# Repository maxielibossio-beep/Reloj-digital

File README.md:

# Reloj-digital
Pcb, esquematico y simulacion del reloj digital

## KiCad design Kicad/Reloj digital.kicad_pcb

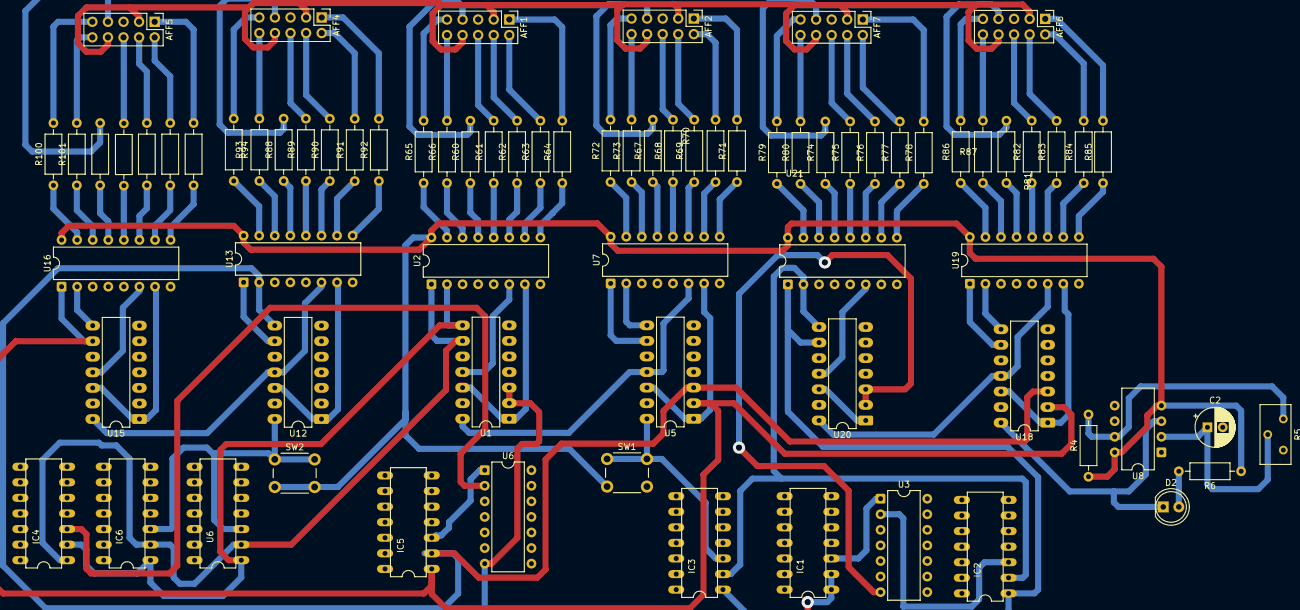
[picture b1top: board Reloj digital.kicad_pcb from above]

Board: 2 copper layers, 77 parts (0 on the bottom side), 125 nets.

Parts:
AFF1, AFF2, AFF4, AFF5, AFF6, AFF7: LTS-6980HR; PinHeader_2x05_P2.54mm_Vertical
C2: 100uF; CP_Radial_D6.3mm_P2.50mm
D2: LED; LED_D5.0mm
IC1, IC2, IC3, IC4, IC5, IC6: 74LS08; DIL14
R4: 4,7KΩ; R_Axial_DIN0207_L6.3mm_D2.5mm_P10.16mm_Horizontal
R5: 10kΩ; Potentiometer_Bourns_3296Y_Vertical
R6: 220Ω; R_Axial_DIN0207_L6.3mm_D2.5mm_P10.16mm_Horizontal
R60, R61, R62, R63, R64, R65, R66, R67, R68, R69, R70, R71, R72, R73, R74, R75, R76, R77, R78, R79, R80, R81, R82, R83, R84, R85, R86, R87, R88, R89, R90, R91, R92, R93, R94, R95, R96, R97, R98, R99, R100, R101: 330R; R_Axial_DIN0207_L6.3mm_D2.5mm_P10.16mm_Horizontal
SW1, SW2: SW_Push; SW_PUSH_6mm
U1, U5, U12, U15, U18, U20: 74LS90; DIP-14_W7.62mm_LongPads
U2, U7, U13, U16, U19, U21: 74LS47; DIP-16_W7.62mm
U3, U6: 74AUC2G32; DIP-14_W7.62mm
U6#2: 74LS08; DIL14
U8: 555; CERDIP-8_W7.62mm_SideBrazed

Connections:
CKA: D2.1 (K), U8.3 (Output), U18.14 (CP0)
GND: C2.2, U1.6 (R9(1)), U1.7 (R9(2)), U2.8 (GND), U5.6 (R9(1)), U5.7 (R9(2)), U7.8 (GND), U8.1 (GND), U12.6 (R9(1)), U12.7 (R9(2)), U13.8 (GND), U15.6 (R9(1)), U15.7 (R9(2)), U16.8 (GND), U18.6 (R9(1)), U18.7 (R9(2)), U19.8 (GND), U20.6 (R9(1)), U20.7 (R9(2)), U21.8 (GND)
unnamed: AFF1.7 (a), R60.2
unnamed: AFF1.6 (b), R61.2
unnamed: AFF1.4 (c), R62.2
unnamed: AFF1.2 (d), R63.2
unnamed: AFF1.1 (e), R64.2
unnamed: AFF1.9 (f), R65.2
unnamed: AFF1.10 (g), R66.2
unnamed: AFF2.7 (a), R67.2
unnamed: AFF2.6 (b), R68.2
unnamed: AFF2.4 (c), R69.2
unnamed: AFF2.2 (d), R70.2
unnamed: AFF2.1 (e), R71.2
unnamed: AFF2.9 (f), R72.2
unnamed: AFF2.10 (g), R73.2
unnamed: AFF4.7 (a), R88.2
unnamed: AFF4.6 (b), R89.2
unnamed: AFF4.4 (c), R90.2
unnamed: AFF4.2 (d), R91.2
unnamed: AFF4.1 (e), R92.2
unnamed: AFF4.9 (f), R93.2
unnamed: AFF4.10 (g), R94.2
unnamed: AFF5.7 (a), R95.2
unnamed: AFF5.6 (b), R96.2
unnamed: AFF5.4 (c), R97.2
unnamed: AFF5.2 (d), R98.2
unnamed: AFF5.1 (e), R99.2
unnamed: AFF5.9 (f), R100.2
unnamed: AFF5.10 (g), R101.2
unnamed: AFF6.7 (a), R81.2
unnamed: AFF6.6 (b), R82.2
unnamed: AFF6.4 (c), R83.2
unnamed: AFF6.2 (d), R84.2
unnamed: AFF6.1 (e), R85.2
unnamed: AFF6.9 (f), R86.2
unnamed: AFF6.10 (g), R87.2
unnamed: AFF7.7 (a), R74.2
unnamed: AFF7.6 (b), R75.2
unnamed: AFF7.4 (c), R76.2
unnamed: AFF7.2 (d), R77.2
unnamed: AFF7.1 (e), R78.2
unnamed: AFF7.9 (f), R79.2
unnamed: AFF7.10 (g), R80.2
unnamed: D2.2 (A), R6.2
unnamed: IC1.3, U3.1
unnamed: IC2.3, U3.2
unnamed: IC4.3, U6.2
unnamed: IC5.3, U6.1
unnamed: AFF1.3 (C.K.), AFF1.8 (C.K.), AFF2.3 (C.K.), AFF2.8 (C.K.), AFF4.3 (C.K.), AFF4.8 (C.K.), AFF5.3 (C.K.), AFF5.8 (C.K.), AFF6.3 (C.K.), AFF6.8 (C.K.), AFF7.3 (C.K.), AFF7.8 (C.K.)
unnamed: U1.14 (CP0), U5.11 (Q3), U7.6 (D)
unnamed: U1.1 (CP1..3), U1.12 (Q0), U2.7 (A)
unnamed: IC4.1, IC6.2, U1.9 (Q1), U2.1 (B), U6#2.2
unnamed: IC4.2, IC6.1, U1.8 (Q2), U2.2 (C), U6#2.1
unnamed: U1.11 (Q3), U2.6 (D)
unnamed: IC1.1, IC1.2, U1.2 (R0(1)), U1.3 (R0(2)), U6.7
unnamed: R60.1, U2.13 (a)
unnamed: R61.1, U2.12 (b)
unnamed: R62.1, U2.11 (c)
unnamed: R63.1, U2.10 (d)
unnamed: R64.1, U2.9 (e)
unnamed: R65.1, U2.15 (f)
unnamed: R66.1, U2.14 (g)
unnamed: IC3.3, SW1.1, U5.14 (CP0)
unnamed: U5.1 (CP1..3), U5.12 (Q0), U7.7 (A)
unnamed: U5.9 (Q1), U7.1 (B)
unnamed: U5.8 (Q2), U7.2 (C)
unnamed: R67.1, U7.13 (a)
unnamed: R68.1, U7.12 (b)
unnamed: R69.1, U7.11 (c)
unnamed: R70.1, U7.10 (d)
unnamed: R71.1, U7.9 (e)
unnamed: R72.1, U7.15 (f)
unnamed: R73.1, U7.14 (g)
unnamed: R4.2, R5.3, U8.7 (Discharge)
unnamed: C2.1, R5.2, U8.2 (Trigger), U8.6 (Threshold)
unnamed: IC6.3, SW2.1, U6#2.3, U12.14 (CP0)
unnamed: U12.1 (CP1..3), U12.12 (Q0), U13.7 (A)
unnamed: U12.9 (Q1), U13.1 (B)
unnamed: IC5.2, U5.3 (R0(2)), U12.8 (Q2), U13.2 (C), U18.3 (R0(2))
unnamed: U12.11 (Q3), U13.6 (D), U15.14 (CP0)
unnamed: U12.2 (R0(1)), U15.2 (R0(1))
unnamed: U12.3 (R0(2)), U15.3 (R0(2))
unnamed: R88.1, U13.13 (a)
unnamed: R89.1, U13.12 (b)
unnamed: R90.1, U13.11 (c)
unnamed: R91.1, U13.10 (d)
unnamed: R92.1, U13.9 (e)
unnamed: R93.1, U13.15 (f)
unnamed: R94.1, U13.14 (g)
unnamed: U15.1 (CP1..3), U15.12 (Q0), U16.7 (A)
unnamed: IC5.1, U5.2 (R0(1)), U15.9 (Q1), U16.1 (B), U18.2 (R0(1))
unnamed: U15.8 (Q2), U16.2 (C)
unnamed: U15.11 (Q3), U16.6 (D)
unnamed: R95.1, U16.13 (a)
unnamed: R96.1, U16.12 (b)
unnamed: R97.1, U16.11 (c)
unnamed: R98.1, U16.10 (d)
unnamed: R99.1, U16.9 (e)
unnamed: R100.1, U16.15 (f)
unnamed: R101.1, U16.14 (g)
unnamed: U18.1 (CP1..3), U18.12 (Q0), U19.7 (A)
unnamed: U18.9 (Q1), U19.1 (B)
unnamed: U18.8 (Q2), U19.2 (C)
unnamed: U18.11 (Q3), U19.6 (D), U20.14 (CP0)
unnamed: R81.1, U19.13 (a)
unnamed: R82.1, U19.12 (b)
unnamed: R83.1, U19.11 (c)
unnamed: R84.1, U19.10 (d)
unnamed: R85.1, U19.9 (e)
unnamed: R86.1, U19.15 (f)
unnamed: R87.1, U19.14 (g)
unnamed: U20.1 (CP1..3), U20.12 (Q0), U21.7 (A)
unnamed: IC2.1, IC3.1, U20.9 (Q1), U21.1 (B)
unnamed: IC2.2, IC3.2, U20.8 (Q2), U21.2 (C)
unnamed: U20.11 (Q3), U21.6 (D)
unnamed: U3.7, U20.2 (R0(1)), U20.3 (R0(2))
unnamed: R74.1, U21.13 (a)
unnamed: R75.1, U21.12 (b)
unnamed: R76.1, U21.11 (c)
unnamed: R77.1, U21.10 (d)
unnamed: R78.1, U21.9 (e)
unnamed: R79.1, U21.15 (f)
unnamed: R80.1, U21.14 (g)
VCC: R4.1, R6.1, SW1.2, SW2.2, U2.16 (VCC), U7.16 (VCC), U8.4 (Reset), U8.8 (VCC), U13.16 (VCC), U16.16 (VCC), U19.16 (VCC), U21.16 (VCC)

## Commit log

2025-11-07 Create proteus
2025-11-07 Create s
2025-11-14 Rename Reloj digital (pro).kicad_pro to Reloj digital.kicad_pro
